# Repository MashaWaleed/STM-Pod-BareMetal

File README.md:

# Welcome To Masha Pod :)
## Your Fully DIY BareMetal Music Player based on ARM, Utilizing Free RTOS.

## Some photos

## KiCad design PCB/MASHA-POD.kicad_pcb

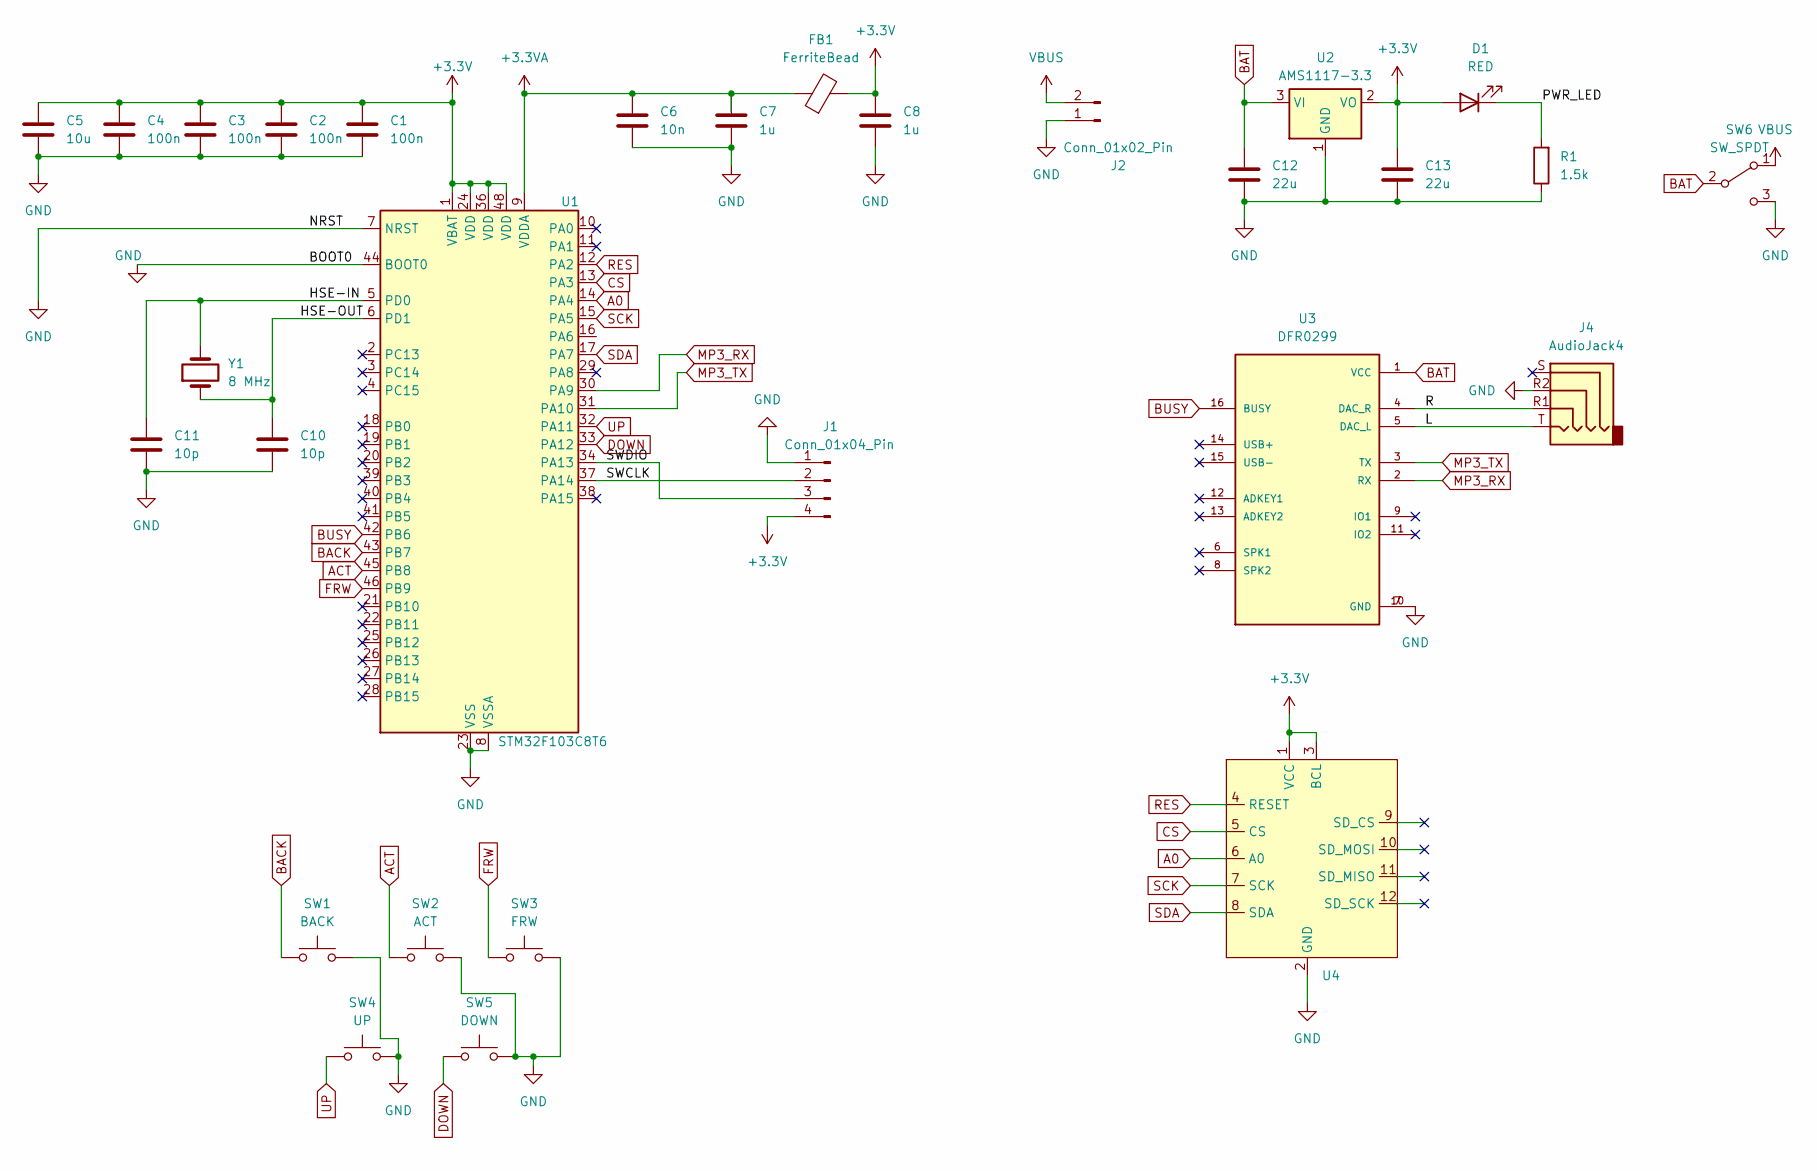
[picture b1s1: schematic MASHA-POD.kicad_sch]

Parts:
C1, C2, C3, C4: 100n; C_1206_3216Metric_Pad1.33x1.80mm_HandSolder
C5: 10u; C_1206_3216Metric_Pad1.33x1.80mm_HandSolder
C6: 10n; C_1206_3216Metric_Pad1.33x1.80mm_HandSolder
C7, C8: 1u; C_1206_3216Metric_Pad1.33x1.80mm_HandSolder
C10, C11: 10p; C_1206_3216Metric_Pad1.33x1.80mm_HandSolder
C12, C13: 22u; C_1206_3216Metric_Pad1.33x1.80mm_HandSolder
D1: RED; LED_1206_3216Metric_Pad1.42x1.75mm_HandSolder
FB1: FerriteBead; L_1206_3216Metric_Pad1.42x1.75mm_HandSolder
J1: Conn_01x04_Pin; PinHeader_1x04_P2.54mm_Horizontal
J2: Conn_01x02_Pin; PhoenixContact_MSTBA_2,5_2-G-5,08_1x02_P5.08mm_Horizontal
J4: AudioJack4; new_conn
R1: 1.5k; R_2010_5025Metric_Pad1.40x2.65mm_HandSolder
SW1: BACK; SW_PUSH_6mm
SW2: ACT; SW_PUSH_6mm
SW3: FRW; SW_PUSH_6mm
SW4: UP; SW_PUSH-12mm
SW5: DOWN; SW_PUSH-12mm
SW6: SW_SPDT; SW_Slide_1P2T_CK_OS102011MS2Q
U1: STM32F103C8T6; LQFP-48_7x7mm_P0.5mm
U2: AMS1117-3.3; SOT-223-3_TabPin2
U3: DFR0299; MODULE_DFR0299
U4: ST7735s
Y1: 8 MHz; Crystal_HC49-U_Vertical

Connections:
+3.3V: C1.1, C2.1, C3.1, C4.1, C5.1, C8.1, C13.1, D1.2 (A), FB1.2, J1.4, U1.1 (VBAT), U1.24 (VDD), U1.36 (VDD), U1.48 (VDD), U2.2 (VO), U4.1 (VCC), U4.3 (BCL)
+3.3VA: C6.1, C7.1, FB1.1, U1.9 (VDDA)
/HSE-IN: C11.1, U1.5 (PD0), Y1.2
/HSE-OUT: C10.1, U1.6 (PD1), Y1.1
/L: J4.T, U3.5 (DAC_L)
/PWR_LED: D1.1 (K), R1.2
/R: J4.R1, U3.4 (DAC_R)
/SWCLK: J1.2, U1.37 (PA14)
/SWDIO: J1.3, U1.34 (PA13)
A0: U1.14 (PA4), U4.6 (A0)
ACT: SW2.1, U1.45 (PB8)
BACK: SW1.1, U1.43 (PB7)
BAT: C12.1, SW6.2 (B), U2.3 (VI), U3.1 (VCC)
BUSY: U1.42 (PB6), U3.16 (BUSY)
CS: U1.13 (PA3), U4.5 (CS)
DOWN: SW5.1, U1.33 (PA12)
FRW: SW3.1, U1.46 (PB9)
GND: C1.2, C2.2, C3.2, C4.2, C5.2, C6.2, C7.2, C8.2, C10.2, C11.2, C12.2, C13.2, J1.1, J2.1, J4.R2, R1.1, SW1.2, SW2.2, SW3.2, SW4.2, SW5.2, SW6.3 (C), U1.7 (NRST), U1.8 (VSSA), U1.23 (VSS), U1.35 (VSS), U1.44 (BOOT0), U1.47 (VSS), U2.1 (GND), U3.7 (GND), U3.10 (GND), U4.2 (GND)
MP3_RX: U1.30 (PA9), U3.2 (RX)
MP3_TX: U1.31 (PA10), U3.3 (TX)
RES: U1.12 (PA2), U4.4 (RESET)
SCK: U1.15 (PA5), U4.7 (SCK)
SDA: U1.17 (PA7), U4.8 (SDA)
UP: SW4.1, U1.32 (PA11)
VBUS: J2.2, SW6.1 (A)

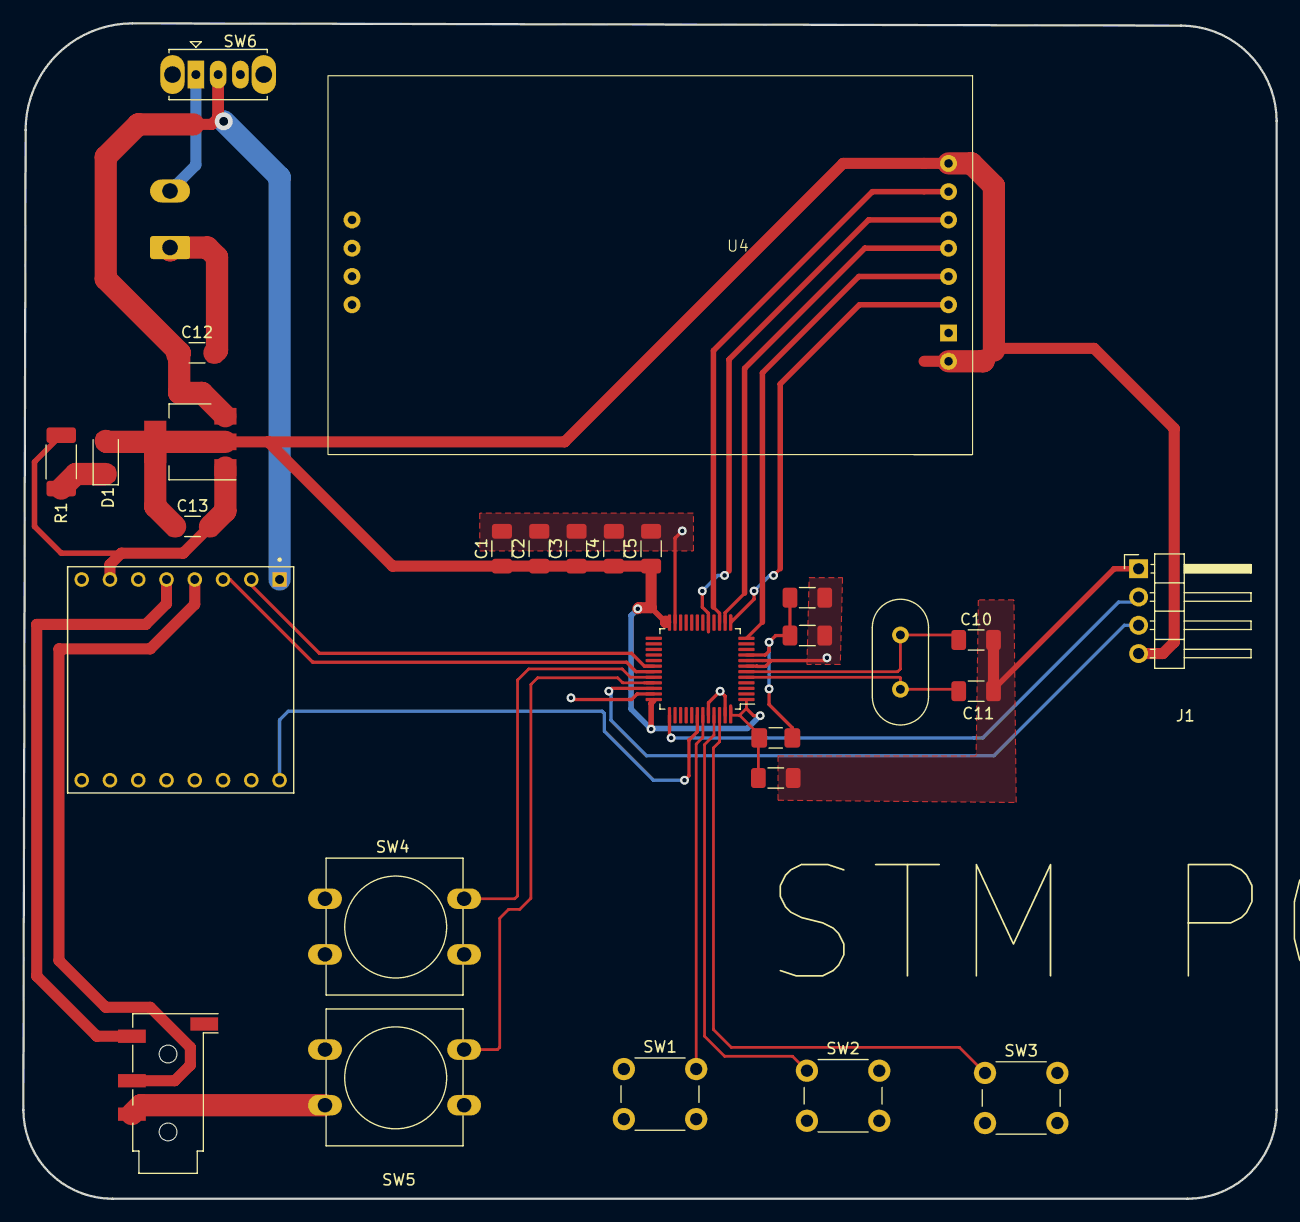
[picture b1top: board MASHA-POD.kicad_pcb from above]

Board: 2 copper layers, 112.6 x 105.6 mm, 29 parts (1 on the bottom side), 25 nets.

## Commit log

2024-02-14 V0.1
2024-02-14 photo
2024-02-20 Final
